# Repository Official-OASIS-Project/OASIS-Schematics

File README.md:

# OASIS-Schematics
EAGLE Schematics and Board files

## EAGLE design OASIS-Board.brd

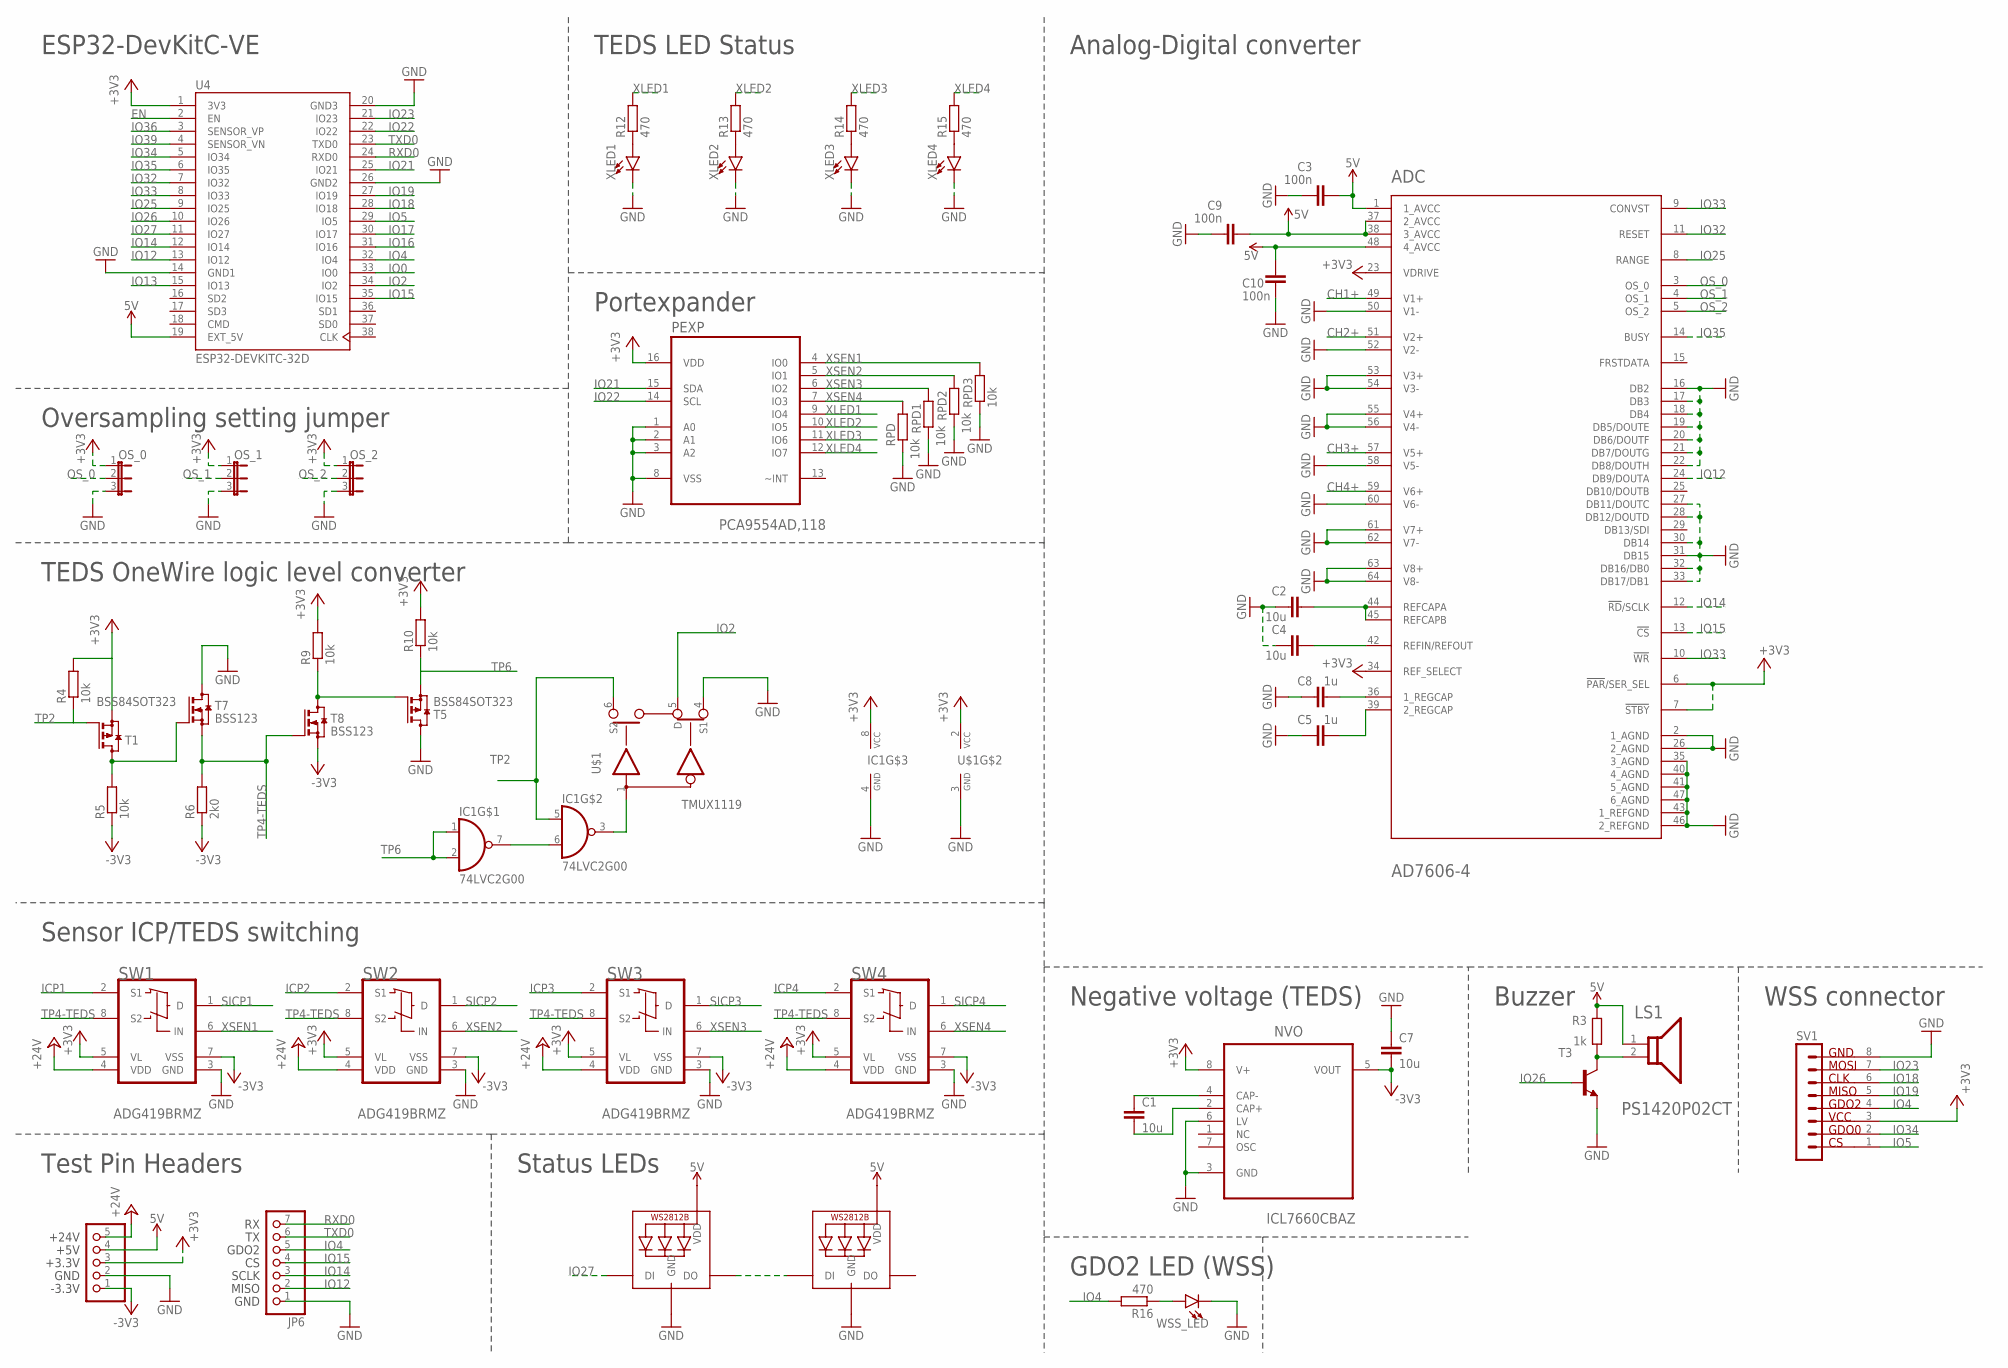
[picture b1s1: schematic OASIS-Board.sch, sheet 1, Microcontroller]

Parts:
ADC: ANALOG_DEVICES_AD7606-4ANALOG_DEVICES_AD7606-4_0_0; ANALOG_DEVICES_AD7606-4_0
C1, C2, C4, C7: 10u; C0603
C3, C9, C10: 100n; C0603
C5, C8: 1u; C0603
IC1: 74LVC2G00; TEXAS_INSTRUMENTS_SN74LVC2G00DCUT_2
JP5: PINHD-1X5; 1X05
JP6: PINHD-1X7; 1X07
LS1: TDK_PS1420P02CTTDK_PS1420P02CT_0_0; TDK_PS1420P02CT_0
NVO: ICL7660CBAZ; SOIC127P600X175-8N
OS_0, OS_1, OS_2: JP2E; JP2
PEXP: PCA9554AD,118; SOIC127P1032X265-16N
R3: 1k; R0603
R4, R5, R9, R10: 10k; R0603_MAYR
R6: 2k0; R0603_MAYR
R12, R13, R14, R15, R16: 470; R0603
RPD, RPD1, RPD2, RPD3: 10k; R0603
STATUS: WS2812B5050; WS2812B
SV1: MA08-1
SW1, SW2, SW3, SW4: ANALOG_DEVICES_ADG419BRMZANALOG_DEVICES_ADG419BRM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; ANALOG_DEVICES_ADG419BRMZ_0
T1, T5: BSS84SOT323; SOT323
T3: BCF32-NPN-SOT23-BEC; SOT23-BEC
T7, T8: BSS123; SOT23
U4: ESP32-DEVKITC-32D; MODULE_ESP32-DEVKITC-32D
U$1: TMUX1119; TEXAS_INSTRUMENTS_TMUX1119DCKR_3
WLAN: WS2812B5050; WS2812B
WSS_LED: LED0603; LED-0603
XLED1, XLED2, XLED3, XLED4: LED0603; LED-0603

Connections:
5V: ADC.1 (1_AVCC), ADC.37 (2_AVCC), ADC.38 (3_AVCC), ADC.48 (4_AVCC), C3.2, C9.2, C10.2, JP5.4, LS1.1, R3.2, STATUS.1-VDD (VDD), U4.19 (EXT_5V), WLAN.1-VDD (VDD); also elsewhere on the board
+3V3: ADC.6 (!PAR!/SER_SEL), ADC.7 (!STBY!), ADC.23 (VDRIVE), ADC.34 (REF_SELECT), IC1.8 (VCC), JP5.3, NVO.8 (V+), OS_0.1, OS_1.1, OS_2.1, PEXP.16 (VDD), R4.2, R9.2, R10.2, SV1.3, SW1.5 (VL), SW2.5 (VL), SW3.5 (VL), SW4.5 (VL), T1.3 (S), U4.1 (3V3), U$1.2 (VCC)
+24V: JP5.5, SW1.4 (VDD), SW2.4 (VDD), SW3.4 (VDD), SW4.4 (VDD); also elsewhere on the board
CH1+: ADC.49 (V1+); also elsewhere on the board
CH2+: ADC.51 (V2+); also elsewhere on the board
CH3+: ADC.57 (V5+); also elsewhere on the board
CH4+: ADC.59 (V6+); also elsewhere on the board
EN: U4.2 (EN)
GND: ADC.2 (1_AGND), ADC.16 (DB2), ADC.17 (DB3), ADC.18 (DB4), ADC.19 (DB5/DOUTE), ADC.20 (DB6/DOUTF), ADC.21 (DB7/DOUTG), ADC.22 (DB8/DOUTH), ADC.26 (2_AGND), ADC.27 (DB11/DOUTC), ADC.28 (DB12/DOUTD), ADC.30 (DB14), ADC.31 (DB15), ADC.32 (DB16/DB0), ADC.33 (DB17/DB1), ADC.35 (3_AGND), ADC.40 (4_AGND), ADC.41 (5_AGND), ADC.43 (1_REFGND), ADC.46 (2_REFGND), ADC.47 (6_AGND), ADC.50 (V1-), ADC.52 (V2-), ADC.53 (V3+), ADC.54 (V3-), ADC.55 (V4+), ADC.56 (V4-), ADC.58 (V5-), ADC.60 (V6-), ADC.61 (V7+), ADC.62 (V7-), ADC.63 (V8+), ADC.64 (V8-), C2.1, C3.1, C4.1, C5.1, C7.1, C8.1, C9.1, C10.1, IC1.4 (GND), JP5.2, JP6.1, NVO.3 (GND), NVO.6 (LV), OS_0.3, OS_1.3, OS_2.3, PEXP.1 (A0), PEXP.2 (A1), PEXP.3 (A2), PEXP.8 (VSS), RPD.1, RPD1.1, RPD2.1, RPD3.1, STATUS.3-GND (GND), SV1.8, SW1.3 (GND), SW2.3 (GND), SW3.3 (GND), SW4.3 (GND), T3.E, T5.1 (D), T7.3 (D), U4.14 (GND1), U4.20 (GND3), U4.26 (GND2), U$1.3 (GND), U$1.4 (S1), WLAN.3-GND (GND), WSS_LED.C, XLED1.C, XLED2.C, XLED3.C, XLED4.C; also elsewhere on the board
ICP1: SW1.2 (S1); also elsewhere on the board
ICP2: SW2.2 (S1); also elsewhere on the board
ICP3: SW3.2 (S1); also elsewhere on the board
ICP4: SW4.2 (S1); also elsewhere on the board
IO0: U4.33 (IO0)
IO2: U4.34 (IO2), U$1.5 (D)
IO4: JP6.5, R16.2, SV1.4, U4.32 (IO4)
IO5: SV1.1, U4.29 (IO5)
IO12: ADC.24 (DB9/DOUTA), JP6.2, U4.13 (IO12)
IO13: U4.15 (IO13)
IO14: ADC.12 (!RD!/SCLK), JP6.3, U4.12 (IO14)
IO15: ADC.13 (!CS!), JP6.4, U4.35 (IO15)
IO16: U4.31 (IO16)
IO17: U4.30 (IO17)
IO18: SV1.6, U4.28 (IO18)
IO19: SV1.5, U4.27 (IO19)
IO21: PEXP.15 (SDA), U4.25 (IO21)
IO22: PEXP.14 (SCL), U4.22 (IO22)
IO23: SV1.7, U4.21 (IO23)
IO25: ADC.8 (RANGE), U4.9 (IO25)
IO26: T3.B, U4.10 (IO26)
IO27: STATUS.4-DIN (DI), U4.11 (IO27)
IO32: ADC.11 (RESET), U4.7 (IO32)
IO33: ADC.9 (CONVST), ADC.10 (!WR!), U4.8 (IO33)
IO34: SV1.2, U4.5 (IO34)
IO35: ADC.14 (BUSY), U4.6 (IO35)
IO36: U4.3 (SENSOR_VP)
IO39: U4.4 (SENSOR_VN)
unnamed: R16.1, WSS_LED.A
unnamed: LS1.2, R3.1, T3.C
unnamed: ADC.36 (1_REGCAP), C8.2
unnamed: STATUS.2-DOUT (DO), WLAN.4-DIN (DI)
unnamed: C1.1, NVO.4 (CAP-)
unnamed: ADC.44 (REFCAPA), ADC.45 (REFCAPB), C2.2
unnamed: R9.1, T5.2 (G), T8.3 (D)
unnamed: IC1.3 (O), U$1.1 (IN)
unnamed: ADC.39 (2_REGCAP), C5.2
unnamed: IC1.6 (I1), IC1.7 (O)
unnamed: R5.2, T1.1 (D), T7.1 (G)
unnamed: C1.2, NVO.2 (CAP+)
unnamed: R12.1, XLED1.A
unnamed: R13.1, XLED2.A
unnamed: ADC.42 (REFIN/REFOUT), C4.2
unnamed: R14.1, XLED3.A
unnamed: R15.1, XLED4.A
OS_0: ADC.3 (OS_0), OS_0.2
OS_1: ADC.4 (OS_1), OS_1.2
OS_2: ADC.5 (OS_2), OS_2.2
RXD0: JP6.7, U4.24 (RXD0)
SICP1: SW1.1 (D); also elsewhere on the board
SICP2: SW2.1 (D); also elsewhere on the board
SICP3: SW3.1 (D); also elsewhere on the board
SICP4: SW4.1 (D); also elsewhere on the board
TP2: IC1.5 (I0), R4.1, T1.2 (G), U$1.6 (S2)
TP4-TEDS: R6.2, SW1.8 (S2), SW2.8 (S2), SW3.8 (S2), SW4.8 (S2), T7.2 (S), T8.1 (G)
TP6: IC1.1 (I0), IC1.2 (I1), R10.1, T5.3 (S)
TXD0: JP6.6, U4.23 (TXD0)
V-: C7.2, JP5.1, NVO.5 (VOUT), R5.1, R6.1, SW1.7 (VSS), SW2.7 (VSS), SW3.7 (VSS), SW4.7 (VSS), T8.2 (S)
XLED1: PEXP.9 (IO4), R12.2
XLED2: PEXP.10 (IO5), R13.2
XLED3: PEXP.11 (IO6), R14.2
XLED4: PEXP.12 (IO7), R15.2
XSEN1: PEXP.4 (IO0), RPD3.2, SW1.6 (IN)
XSEN2: PEXP.5 (IO1), RPD2.2, SW2.6 (IN)
XSEN3: PEXP.6 (IO2), RPD1.2, SW3.6 (IN)
XSEN4: PEXP.7 (IO3), RPD.2, SW4.6 (IN)

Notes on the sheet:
ESP32-DevKitC-VE
Analog-Digital converter
Buzzer
TEDS OneWire logic level converter
WSS connector
Sensor ICP/TEDS switching
Negative voltage (TEDS)
Portexpander
Oversampling setting jumper
TEDS LED Status
GDO2 LED (WSS)
Test Pin Headers
Status LEDs

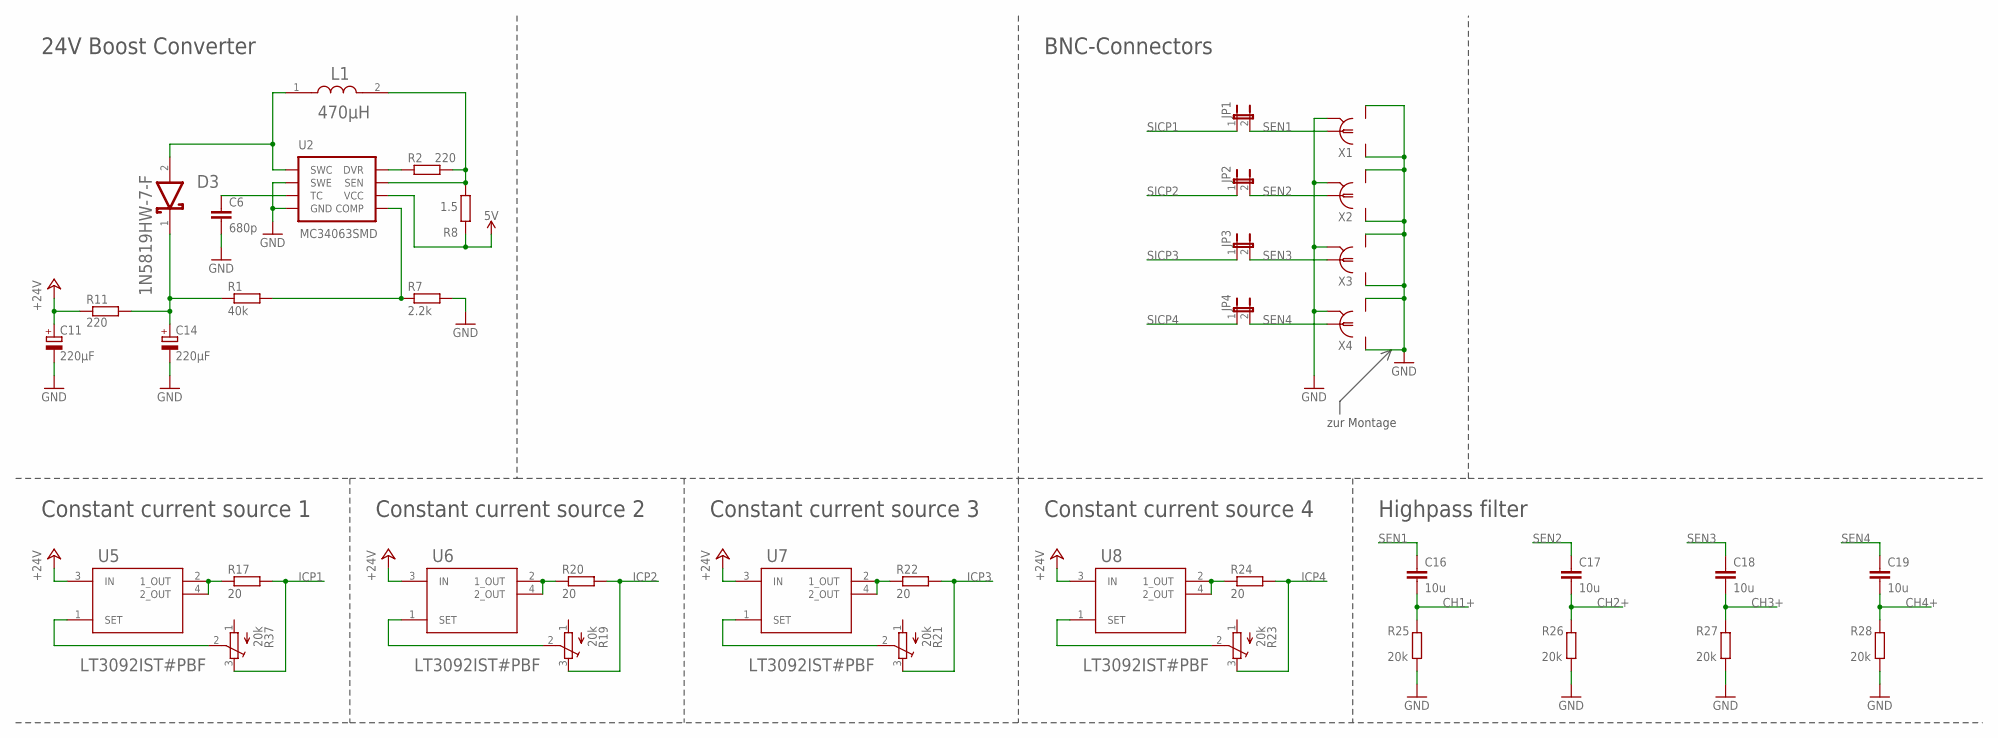
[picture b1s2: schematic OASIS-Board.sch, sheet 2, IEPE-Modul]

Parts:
C6: 680p; C0603
C11, C14: 220µF; 153CLV-1012
C16, C17, C18, C19: 10u; C0603
D3: DIODES_1N5819HW-7-FDIODES_1N5819HW-7-F_0_1; DIODES_1N5819HW-7-F_1
JP1, JP2, JP3, JP4: JP1E; JP1
L1: BOURNS_SRR1260-470MBOURNS_SRR1260-470M_0_0; BOURNS_SRR1260-470M_0
R1: 40k; R0603
R2, R11: 220; R0603
R7: 2.2k; R0603
R8: 1.5; R0603
R17, R20, R22, R24: 20; R0603
R19, R21, R23, R37: 20k; SM-42/43W
R25, R26, R27, R28: 20k; R0603
U2: MC34063SMD; SO08
U5, U6, U7, U8: ANALOG_DEVICES_INC_LT3092IST#PBFANALOG_DEVICES_IN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; ANALOG_DEVICES_INC_LT3092IST#PBF_0
X1, X2, X3, X4: BNC; AMP_227161

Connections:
5V: R8.1, U2.6 (VCC); also elsewhere on the board
+24V: C11.+, R11.1, U5.3 (IN), U6.3 (IN), U7.3 (IN), U8.3 (IN); also elsewhere on the board
CH1+: C16.2, R25.2; also elsewhere on the board
CH2+: C17.2, R26.2; also elsewhere on the board
CH3+: C18.2, R27.2; also elsewhere on the board
CH4+: C19.2, R28.2; also elsewhere on the board
GND: C6.2, C11.-, C14.-, R7.2, R25.1, R26.1, R27.1, R28.1, U2.2 (SWE), U2.4 (GND), X1.2, X1.P$1, X1.P$2, X2.2, X2.P$1, X2.P$2, X3.2, X3.P$1, X3.P$2, X4.2, X4.P$1, X4.P$2; also elsewhere on the board
ICP1: R17.2, R37.3 (E); also elsewhere on the board
ICP2: R19.3 (E), R20.2; also elsewhere on the board
ICP3: R21.3 (E), R22.2; also elsewhere on the board
ICP4: R23.3 (E), R24.2; also elsewhere on the board
unnamed: D3.2 (ANODE), L1.1, U2.1 (SWC)
unnamed: C6.1, U2.3 (TC)
unnamed: L1.2, R2.2, R8.2, U2.7 (SEN)
unnamed: R1.2, R7.1, U2.5 (COMP)
unnamed: R2.1, U2.8 (DVR)
unnamed: C14.+, D3.1 (CATHODE), R1.1, R11.2
unnamed: R17.1, U5.2 (1_OUT), U5.4 (2_OUT)
unnamed: R37.2 (S), U5.1 (SET)
unnamed: R20.1, U6.2 (1_OUT), U6.4 (2_OUT)
unnamed: R19.2 (S), U6.1 (SET)
unnamed: R22.1, U7.2 (1_OUT), U7.4 (2_OUT)
unnamed: R21.2 (S), U7.1 (SET)
unnamed: R24.1, U8.2 (1_OUT), U8.4 (2_OUT)
unnamed: R23.2 (S), U8.1 (SET)
SEN1: C16.1, JP1.2, X1.1
SEN2: C17.1, JP2.2, X2.1
SEN3: C18.1, JP3.2, X3.1
SEN4: C19.1, JP4.2, X4.1
SICP1: JP1.1; also elsewhere on the board
SICP2: JP2.1; also elsewhere on the board
SICP3: JP3.1; also elsewhere on the board
SICP4: JP4.1; also elsewhere on the board

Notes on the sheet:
Constant current source 1
BNC-Connectors
zur Montage
24V Boost Converter
Constant current source 2
Constant current source 3
Constant current source 4
Highpass filter

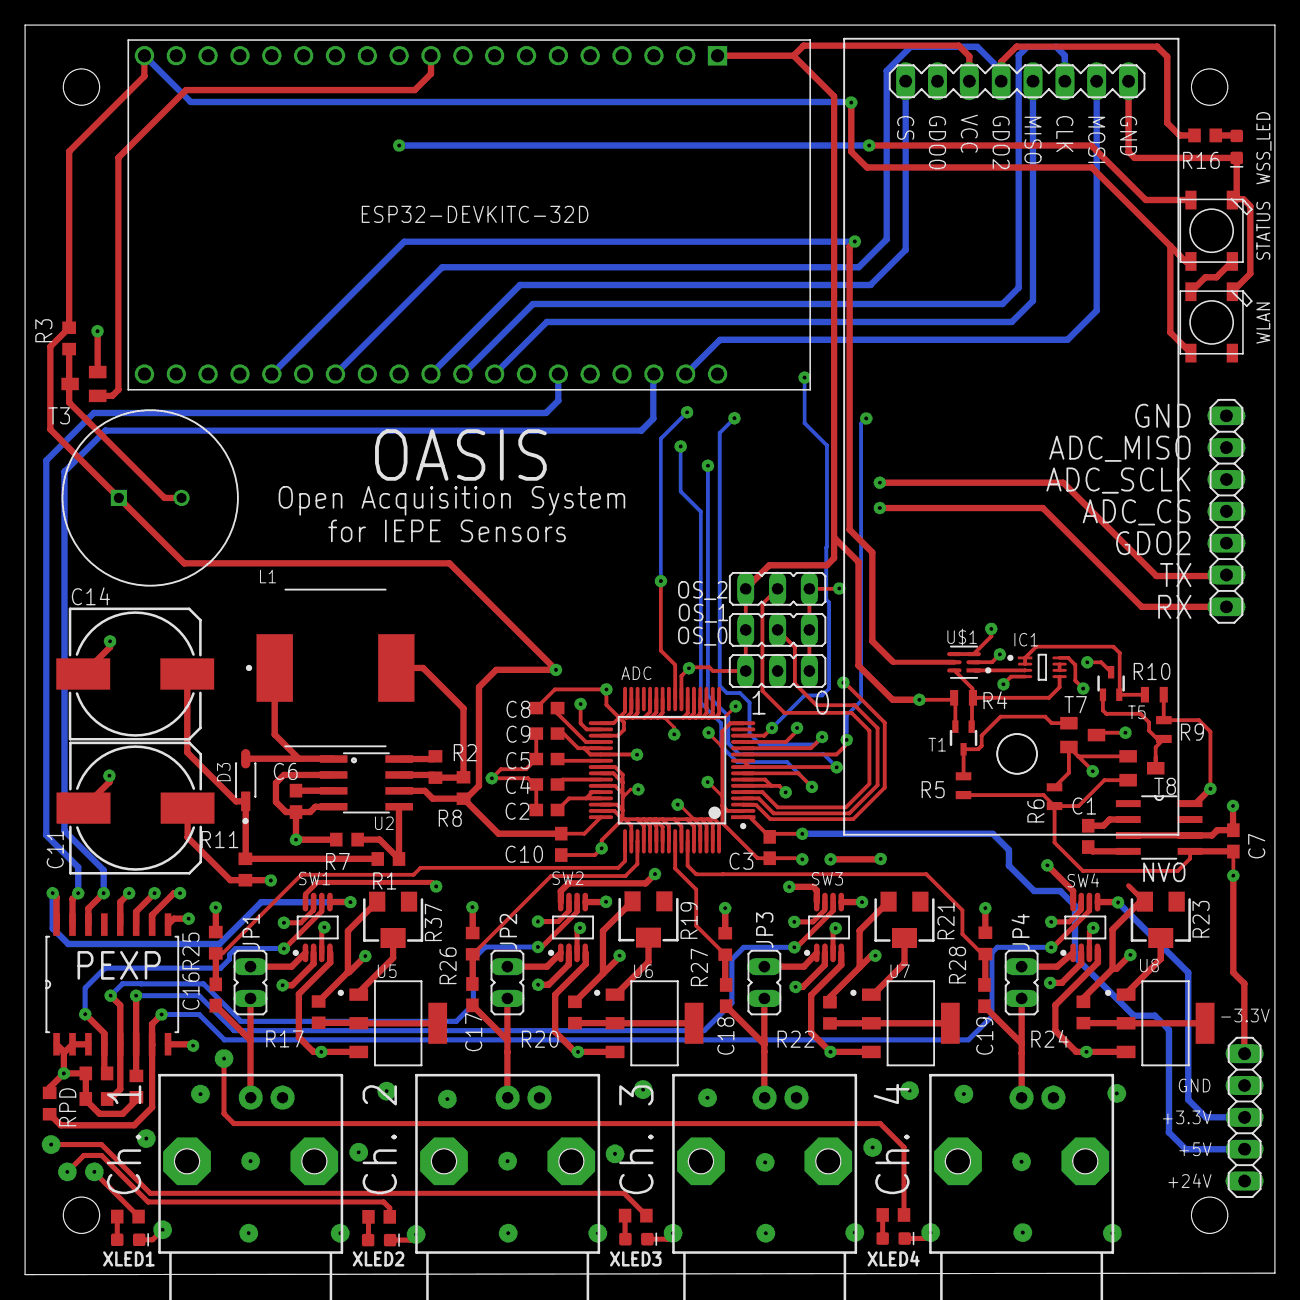
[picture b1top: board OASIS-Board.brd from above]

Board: 4 copper layers, 99.7 x 99.7 mm, 92 parts (0 on the bottom side), 86 nets.

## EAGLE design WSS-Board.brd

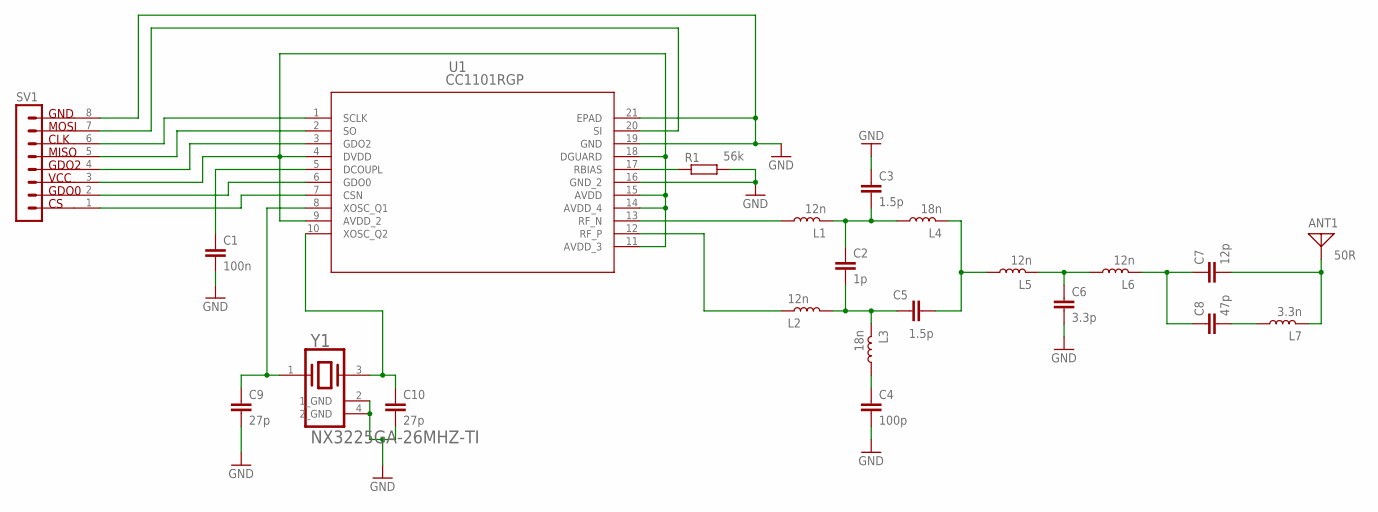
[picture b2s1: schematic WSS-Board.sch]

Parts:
ANT1: 50R; PAD-01
C1: 100n; C0603
C2: 1p; C0603
C3, C5: 1.5p; C0603
C4: 100p; C0603
C6: 3.3p; C0603
C7: 12p; C0603
C8: 47p; C0603
C9, C10: 27p; C0603
L1, L2, L5, L6: 12n; 0603
L3, L4: 18n; 0603
L7: 3.3n; 0603
R1: 56k; R0603
SV1: MA08-1
U1: CC1101RGP; RGP20_2P4X2P4
Y1: NDK_NX3225GA-26MHZ-TINDK_NX3225GA-26MHZ-TI_0_0; NDK_NX3225GA-26MHZ-TI_0

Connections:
CLK: SV1.6, U1.1 (SCLK)
CS: SV1.1, U1.7 (CSN)
GDO0: SV1.2, U1.6 (GDO0)
GDO2: SV1.4, U1.3 (GDO2)
GND: C1.2, C3.1, C4.2, C6.2, C9.2, C10.2, R1.2, SV1.8, U1.16 (GND_2), U1.19 (GND), U1.21 (EPAD), Y1.2 (1_GND), Y1.4 (2_GND)
MISO: SV1.5, U1.2 (SO)
MOSI: SV1.7, U1.20 (SI)
unnamed: R1.1, U1.17 (RBIAS)
unnamed: C1.1, U1.5 (DCOUPL)
unnamed: L1.1, U1.13 (RF_N)
unnamed: L2.2, U1.12 (RF_P)
unnamed: C2.1, C3.2, L1.2, L4.1
unnamed: C4.1, L3.1
unnamed: C2.2, C5.1, L2.1, L3.2
unnamed: C5.2, L4.2, L5.1
unnamed: C6.1, L5.2, L6.1
unnamed: C7.1, C8.1, L6.2
unnamed: C8.2, L7.1
unnamed: ANT1.1, C7.2, L7.2
unnamed: C10.1, U1.10 (XOSC_Q2), Y1.3
unnamed: C9.1, U1.8 (XOSC_Q1), Y1.1
VCC: SV1.3, U1.4 (DVDD), U1.9 (AVDD_2), U1.11 (AVDD_3), U1.14 (AVDD_4), U1.15 (AVDD), U1.18 (DGUARD)

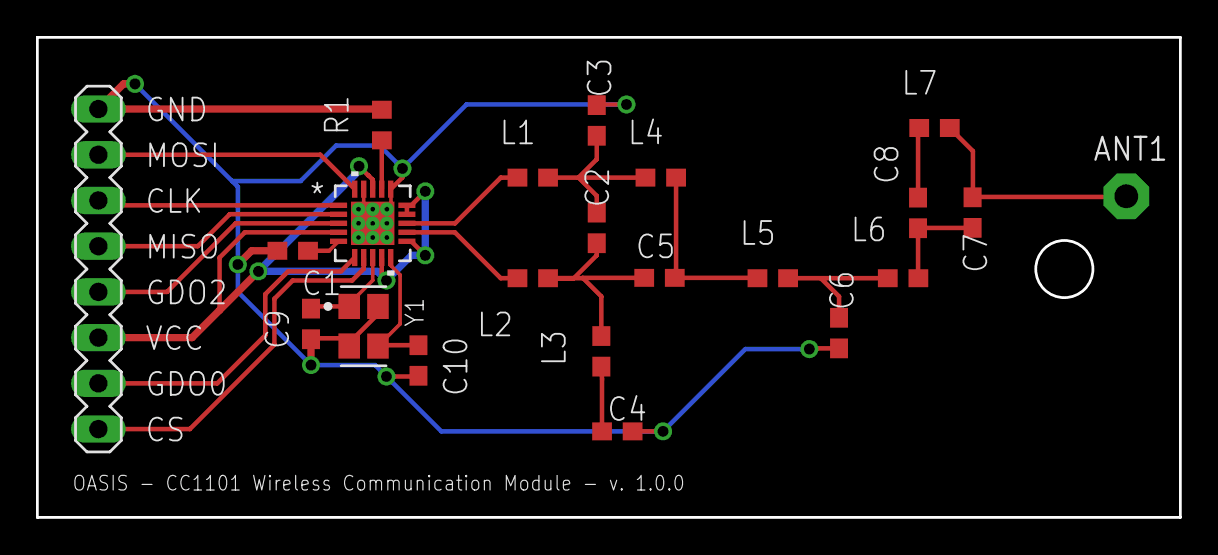
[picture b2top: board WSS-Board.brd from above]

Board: 2 copper layers, 63.5 x 26.7 mm, 22 parts (0 on the bottom side), 22 nets.

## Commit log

2023-01-10 Update .gitignore, OASIS-CC1101-Header.lbr, and 7 more files...
2023-02-02 PDF of Board Schematic

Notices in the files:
parts and their libraries:
SparkFun-IC-Power: Licensing: Creative Commons ShareAlike 4.0 International - https://creativecommons.org/licenses/by-sa/4.0
COPYRIGHT: Copyright (C) 2022 Ultra Librarian. All rights reserved.
